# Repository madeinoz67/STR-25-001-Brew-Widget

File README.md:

# STR-25-001 Brew Widget

ESP32 Based Tilt Hydrometer

## Project Features

- All in one PCB inspired by [iSpindel - DIY electronics Hydrometer](https://www.ispindel.de/)

## Resources

Below are some handy resource links.

* [KiCad](https://www.kicad.org/) is a Cross Platform and Open Source Electronics Design Automation suite.
* [cookiecutter-kicad](https://github.com/madeinoz67/cookiecutter-kicad) a cookiecutter template for KiCad Projects.

## Authors

* **Stephen Eaton** - *Initial Work* - [github](https://github.com/madeinoz67)

See also the list of [contributors](https://github.com/madeinoz67/brew-widget/AUTHORS.rst) who participated in this project.

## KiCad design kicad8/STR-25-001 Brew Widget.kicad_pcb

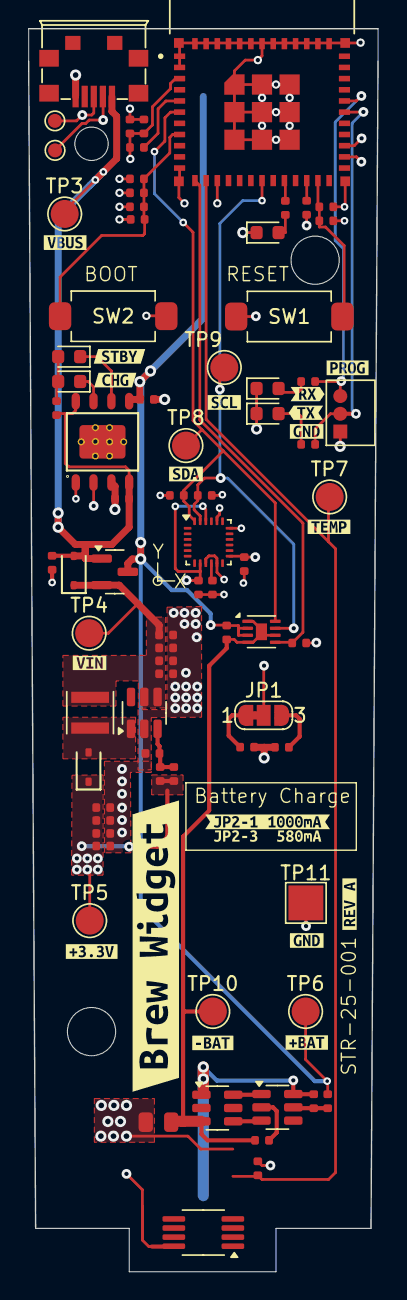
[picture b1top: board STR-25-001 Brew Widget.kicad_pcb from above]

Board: 4 copper layers, 25.0 x 88.9 mm, 95 parts (1 on the bottom side), 36 nets.

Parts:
BT1: 18650; BatteryHolder_Keystone_1042_1x18650
C1, C3, C4, C12, C14, C20, C21: 100nF; C_0402
C2: 4.7uF; C_0402
C5, C6, C7, C8, C10, C15, C18, C19: 10uF; C_0402
C9, C17: 1uF; C_0402
C11, C16: 100pF; C_0402
C13: 10pF; C_0402
D1, D2, D3, D5: RED; LED_0603_1608Metric
D4, D7: B16WS; D_SOD-323
D6: GREEN; LED_0603_1608Metric
J1: USB_B_Micro; MICRO-USB-SMD_5P_C40945
JP1: SolderJumper_3_Bridged12; SolderJumper-3_P1.3mm_Bridged12_RoundedPad1.0x1.5mm_NumberL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
L1: 22uH,540mA; IND_LQH3NPZ220MMEL
PROG1: Pogo Pin 1.27mm; PROG_1x3_1.27
Q1: IRLML6401; SOT-23
Q2: FS8205A; SOT-23-6
R1, R2, R3, R4, R9, R19: 10kΩ; R_0402
R5, R8, R10: 1.5kΩ; R_0402
R6, R7, R18: 4.7kΩ; R_0402
R11: 100kΩ; R_0402
R12, R14: 2kΩ; R_0402
R13: 1.2kΩ; R_0402
R15: 68kΩ; R_0402
R16: 15kΩ; R_0402
R17: 100Ω; R_0402
R20: 0Ω; R_0805
R21: 1kΩ; R_0402
SW1, SW2: SPST 8x3.6; SW_SMD_SPST_8x3.6
TP1, TP2: TestPoint; TestPoint_Pad_D1.0mm
TP3, TP4, TP5, TP6, TP7, TP8, TP9, TP10: TestPoint; TestPoint_Pad_D2.0mm
TP11: TestPoint; TestPoint_Pad_2.5x2.5mm
U1: ESP32-C3-MINI-1-N4
U2: TP4056; ESOP-8_L4.9-W3.9-P1.27-LS6.0-BL-EP
U3: MT3608; SOT-23-6
U4: MPU-6500; InvenSense_QFN-24_3x3mm_P0.4mm_NoMask
U5: MAX17048; TDFN-8-1EP_2x2mm_P0.5mm_EP0.8x1.2mm
U6: DS18B20U; MSOP-8_3x3mm_P0.65mm
U7: DW01A; SOT-23-6
kibuzzard-67835DB7: G***; kibuzzard-67835DB7
kibuzzard-67835E0F: G***; kibuzzard-67835E0F
kibuzzard-67835E03: G***; kibuzzard-67835E03
kibuzzard-67835E3B: G***; kibuzzard-67835E3B
kibuzzard-67837AE8: G***; kibuzzard-67837AE8
kibuzzard-67837E72: G***; kibuzzard-67837E72
kibuzzard-678345AF: G***; kibuzzard-678345AF
kibuzzard-678345CB: G***; kibuzzard-678345CB
kibuzzard-678345D9: G***; kibuzzard-678345D9
kibuzzard-678345E8: G***; kibuzzard-678345E8
kibuzzard-678346A0: G***; kibuzzard-678346A0
kibuzzard-6783457B: G***; kibuzzard-6783457B
kibuzzard-67834543: G***; kibuzzard-67834543
kibuzzard-67834564: G***; kibuzzard-67834564
kibuzzard-67834594: G***; kibuzzard-67834594
kibuzzard-67834607: G***; kibuzzard-67834607
kibuzzard-67834787: G***; kibuzzard-67834787
kibuzzard-67836539: G***; kibuzzard-67836539
kibuzzard-67836544: G***; kibuzzard-67836544

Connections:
+3.3V: C4.1, C5.1, C6.1, C13.1, C14.1, C16.1, C17.1, C18.1, C19.1, D7.1, R1.1, R2.1, R3.1, R4.1, R6.1, R7.1, R9.1, R15.1, R18.1, R19.1, TP5.1, U1.3 (3V3), U4.8 (VDDIO), U4.13 (VDD), U4.22 (nCS), U6.8 (V_{DD})
+BATT: BT1.1 (+), C15.1, C20.1, Q1.3 (D), R17.1, TP6.1, U2.5 (BAT), U5.2 (CELL), U5.3 (VDD)
-BATT: C20.2, Q2.3 (S2), R20.1, R21.2, TP10.1, U5.1 (CTG), U5.4 (GND), U5.6 (QSTRT), U5.9 (EP)
/-BATT_NOPROT: BT1.2 (-), C21.2, Q2.1 (S1), U7.6 (GND)
/FB: C13.2, R15.2, R16.1, U3.3 (FB)
/PROG: JP1.2 (C), U2.2 (PROG)
/VIN: C7.1, C8.1, C9.1, C11.1, D4.1, L1.1, Q1.2 (S), TP4.1, U3.4 (EN), U3.5 (IN)
/VOUT: D7.2, L1.2, U3.1 (SW)
/~CHG: D5.1 (K), U2.7 (~CHRG)
/~STBY: D6.1 (K), U2.6 (~STDBY)
EN: C2.1, C3.1, R3.2, R4.2, SW2.2, U1.8 (EN)
GND: C1.2, C2.2, C3.2, C4.2, C5.2, C6.2, C7.2, C8.2, C9.2, C10.2, C11.2, C12.2, C14.2, C15.2, C16.2, C17.2, C18.2, C19.2, D1.1 (K), D2.1 (K), D3.1 (K), J1.5 (GND), PROG1.1 (GND), R11.2, R13.2, R14.2, R16.2, R20.2, SW1.1, SW2.1, TP11.1, U1.1 (GND), U1.2 (GND), U1.11 (GND), U1.14 (GND), U1.36 (GND), U1.37 (GND), U1.38 (GND), U1.39 (GND), U1.40 (GND), U1.41 (GND), U1.42 (GND), U1.43 (GND), U1.44 (GND), U1.45 (GND), U1.46 (GND), U1.47 (GND), U1.48 (GND), U1.49 (GND_THERMAL), U1.49_2 (GND_THERMAL), U1.49_3 (GND_THERMAL), U1.49_4 (GND_THERMAL), U1.49_5 (GND_THERMAL), U1.49_6 (GND_THERMAL), U1.49_7 (GND_THERMAL), U1.49_8 (GND_THERMAL), U1.49_9 (GND_THERMAL), U1.50 (GND), U1.51 (GND), U1.52 (GND), U1.53 (GND), U2.1 (TEMP), U2.3 (GND), U2.9 (EP), U3.2 (GND), U4.9 (AD0), U4.11 (FSYNC), U4.18 (GND), U4.20 (RESV), U6.4 (GND)
GPIO6: R8.1, U1.20 (IO6)
GPIO9: C1.1, R2.2, SW1.2, U1.23 (IO9)
unnamed: D1.2 (A), R5.2
unnamed: D2.2 (A), R8.2
unnamed: D3.2 (A), R10.2
unnamed: D5.2 (A), D6.2 (A), R12.2
unnamed: JP1.1 (A), R13.1
unnamed: JP1.3 (B), R14.1
unnamed: Q2.6 (G1), U7.1 (OD)
unnamed: Q2.4 (G2), U7.3 (OC)
unnamed: R1.2, U1.5 (IO2)
unnamed: R9.2, U1.22 (IO8)
unnamed: C12.1, U4.10 (REGOUT)
unnamed: R21.1, U7.2 (CS)
unnamed: C21.1, R17.2, U7.5 (VCC)
RX_IN: PROG1.3 (RX), R5.1, U1.31 (IO21/TXD0)
SCL: R6.2, TP9.1, U1.18 (IO4), U4.23 (SCL), U5.7 (SCL)
SDA: R7.2, TP8.1, U1.6 (IO3), U4.24 (SDA), U5.8 (SDA)
TEMP: R18.2, TP7.1, U1.13 (IO1), U6.1 (DQ)
TX_IN: PROG1.2 (TX), R10.1, U1.30 (IO20/RXD0)
USB_D+: J1.3 (D+), TP2.1, U1.27 (IO19/USB_D+)
USB_D-: J1.2 (D-), TP1.1, U1.26 (IO18/USB_D-)
VBUS: C10.1, D4.2, J1.1 (VCC), Q1.1 (G), R11.1, R12.1, TP3.1, U2.4 (VCC), U2.8 (CE)
~BAT_ALERT: R19.2, U1.12 (IO0), U5.5 (~ALRT)

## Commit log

2025-01-04 initial project commit
2025-01-04 FIX - added token to auto-commit
2025-01-04 bumped checkout on github actions
2025-01-04 Update Changelog for PR
2025-01-04 bumped version
2025-01-04 Added github documentation
2025-01-04 updated docs and version
2025-01-04 Update Changelog for tag
2025-01-04 Added github release checklist
2025-01-04 Added mkdocs-autorefs plugin
2025-01-04 updated initial documentation
2025-01-04 updated .gitignore
2025-01-04 Deployed 0393dfe with MkDocs version: 1.6.1
2025-01-04 changes before bed
2025-01-06 Removed unused schematic sheets
2025-01-06 Ready for Schematic Review
2025-01-06 updated references.md
2025-01-06 updated kicad-library
2025-01-09 Started PCB Layout
2025-01-11 PCB routed and all 3d models correct, needs final review
2025-01-11 Added TP labels on top silkscreen
2025-01-11 Fix DRC
2025-01-11 Added Fiducals
2025-01-12 Finalising deisgn, first checks review done
2025-01-12 BOM generated
2025-01-15 Changed to Buck Regulator using MT3406 Changed from DW01A on battery protection to AP9101C due to better low voltage protection

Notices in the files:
kicad8/STR-25-001 Brew Widget.kicad_pcb:
License: CC-A-SA
